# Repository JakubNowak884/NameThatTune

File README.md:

# NameThatTune
Device that allows you to connect with Android phone via bluetoooth and compete between four people in guesing tune.
Four switches are for players. When one of them is pressed music stops playing and LED corresponding to it turns on.
When middle switch is pressed music starts playing and allows players to compete.

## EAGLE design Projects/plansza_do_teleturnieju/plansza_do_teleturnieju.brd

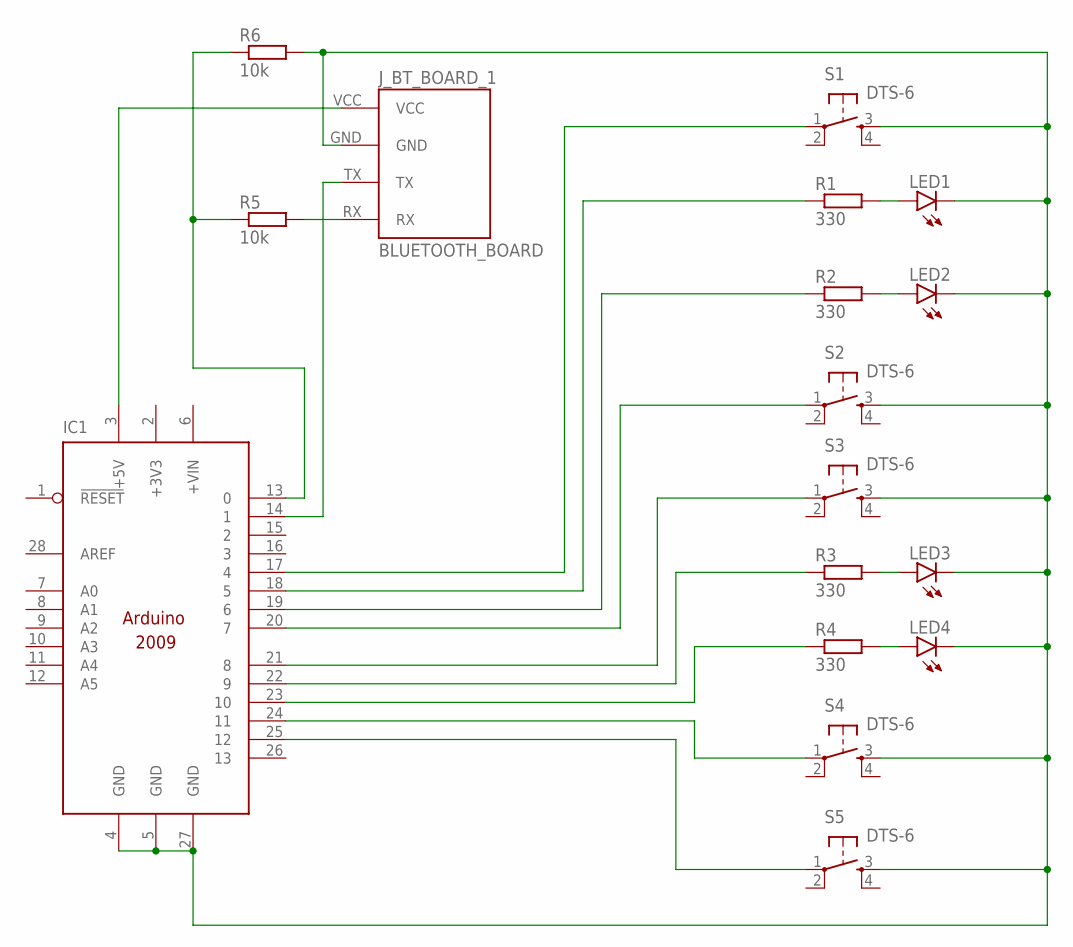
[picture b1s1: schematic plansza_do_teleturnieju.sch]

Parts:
IC1: ARDUINO2009_10; ARDUINO2009
J_BT_BOARD_1: BLUETOOTH_BOARD; BT_BOARD_FOOTPRINT
LED1, LED2, LED3, LED4: LEDLD260; LD260
R1, R2, R3, R4: 330; 0204/7
R5, R6: 10k; 0204/7
S1, S2, S3, S4, S5: DTS-6

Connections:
+3V3: IC1.2 (+3V3)
unnamed: IC1.17 (4), S1.1
unnamed: IC1.18 (5), R1.1
unnamed: IC1.24 (11), S4.1
unnamed: IC1.23 (10), R4.1
unnamed: IC1.21 (8), S3.1
unnamed: IC1.22 (9), R3.1
unnamed: IC1.20 (7), S2.1
unnamed: IC1.19 (6), R2.1
unnamed: IC1.4 (GND), IC1.5 (GND), IC1.27 (GND), J_BT_BOARD_1.GND, LED1.K (C), LED2.K (C), LED3.K (C), LED4.K (C), R6.2, S1.3, S2.3, S3.3, S4.3, S5.3
unnamed: IC1.25 (12), S5.1
unnamed: LED1.A, R1.2
unnamed: IC1.3 (+5V), J_BT_BOARD_1.VCC
unnamed: IC1.13 (0), R5.1, R6.1
unnamed: J_BT_BOARD_1.RX, R5.2
unnamed: LED2.A, R2.2
unnamed: LED3.A, R3.2
unnamed: LED4.A, R4.2
unnamed: IC1.14 (1), J_BT_BOARD_1.TX

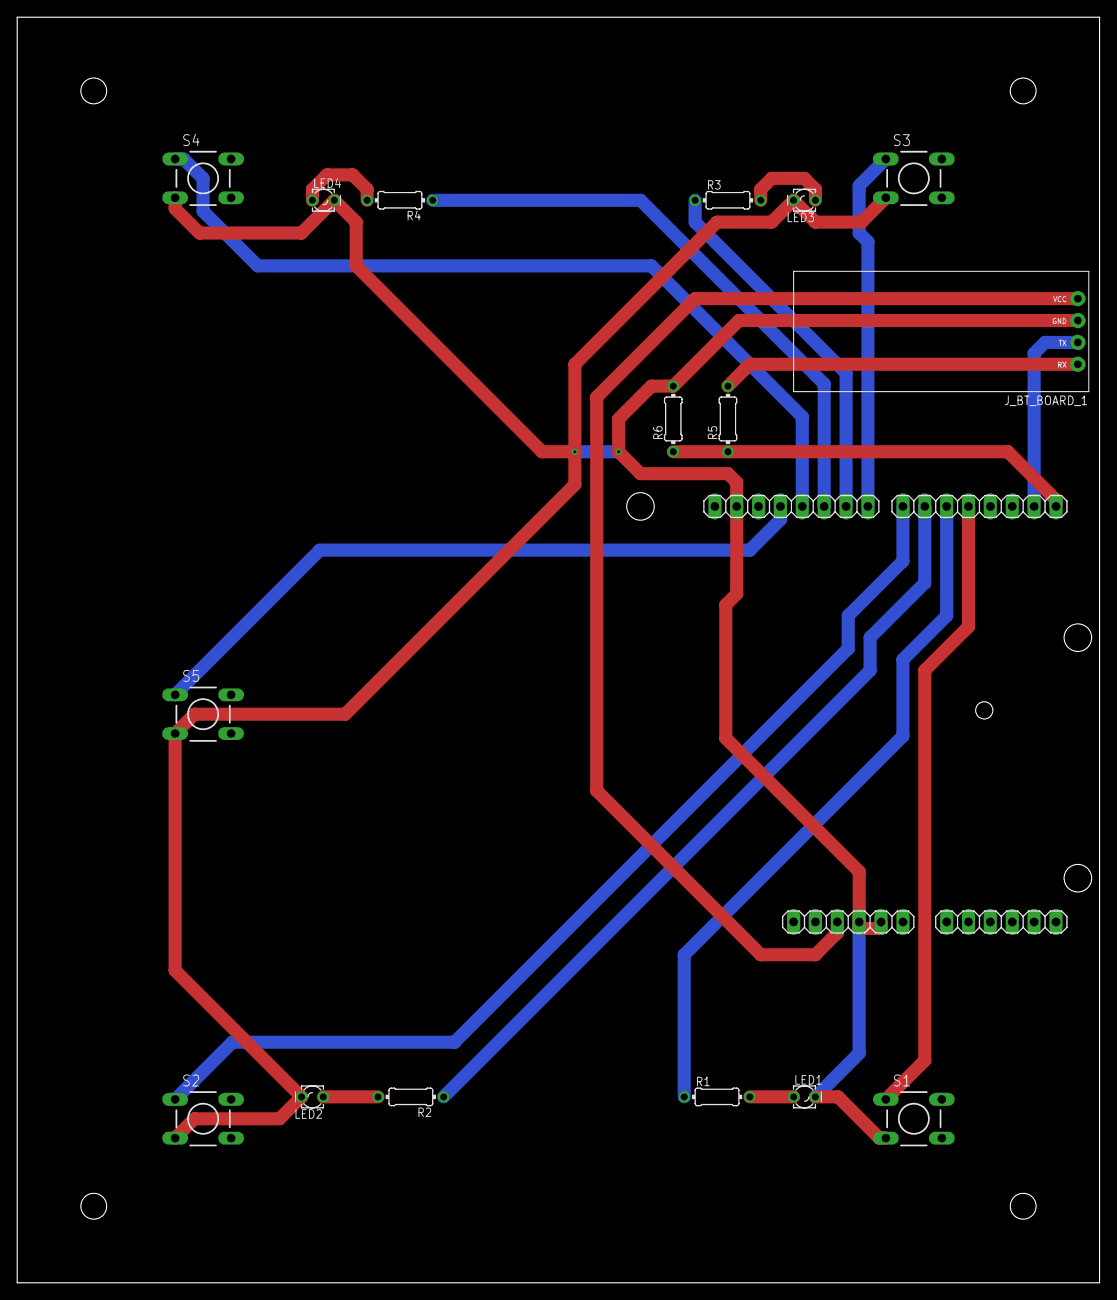
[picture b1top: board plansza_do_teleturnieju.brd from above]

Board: 2 copper layers, 125.7 x 147.0 mm, 17 parts (0 on the bottom side), 18 nets.

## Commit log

2022-02-08 Picture and eagle schema
